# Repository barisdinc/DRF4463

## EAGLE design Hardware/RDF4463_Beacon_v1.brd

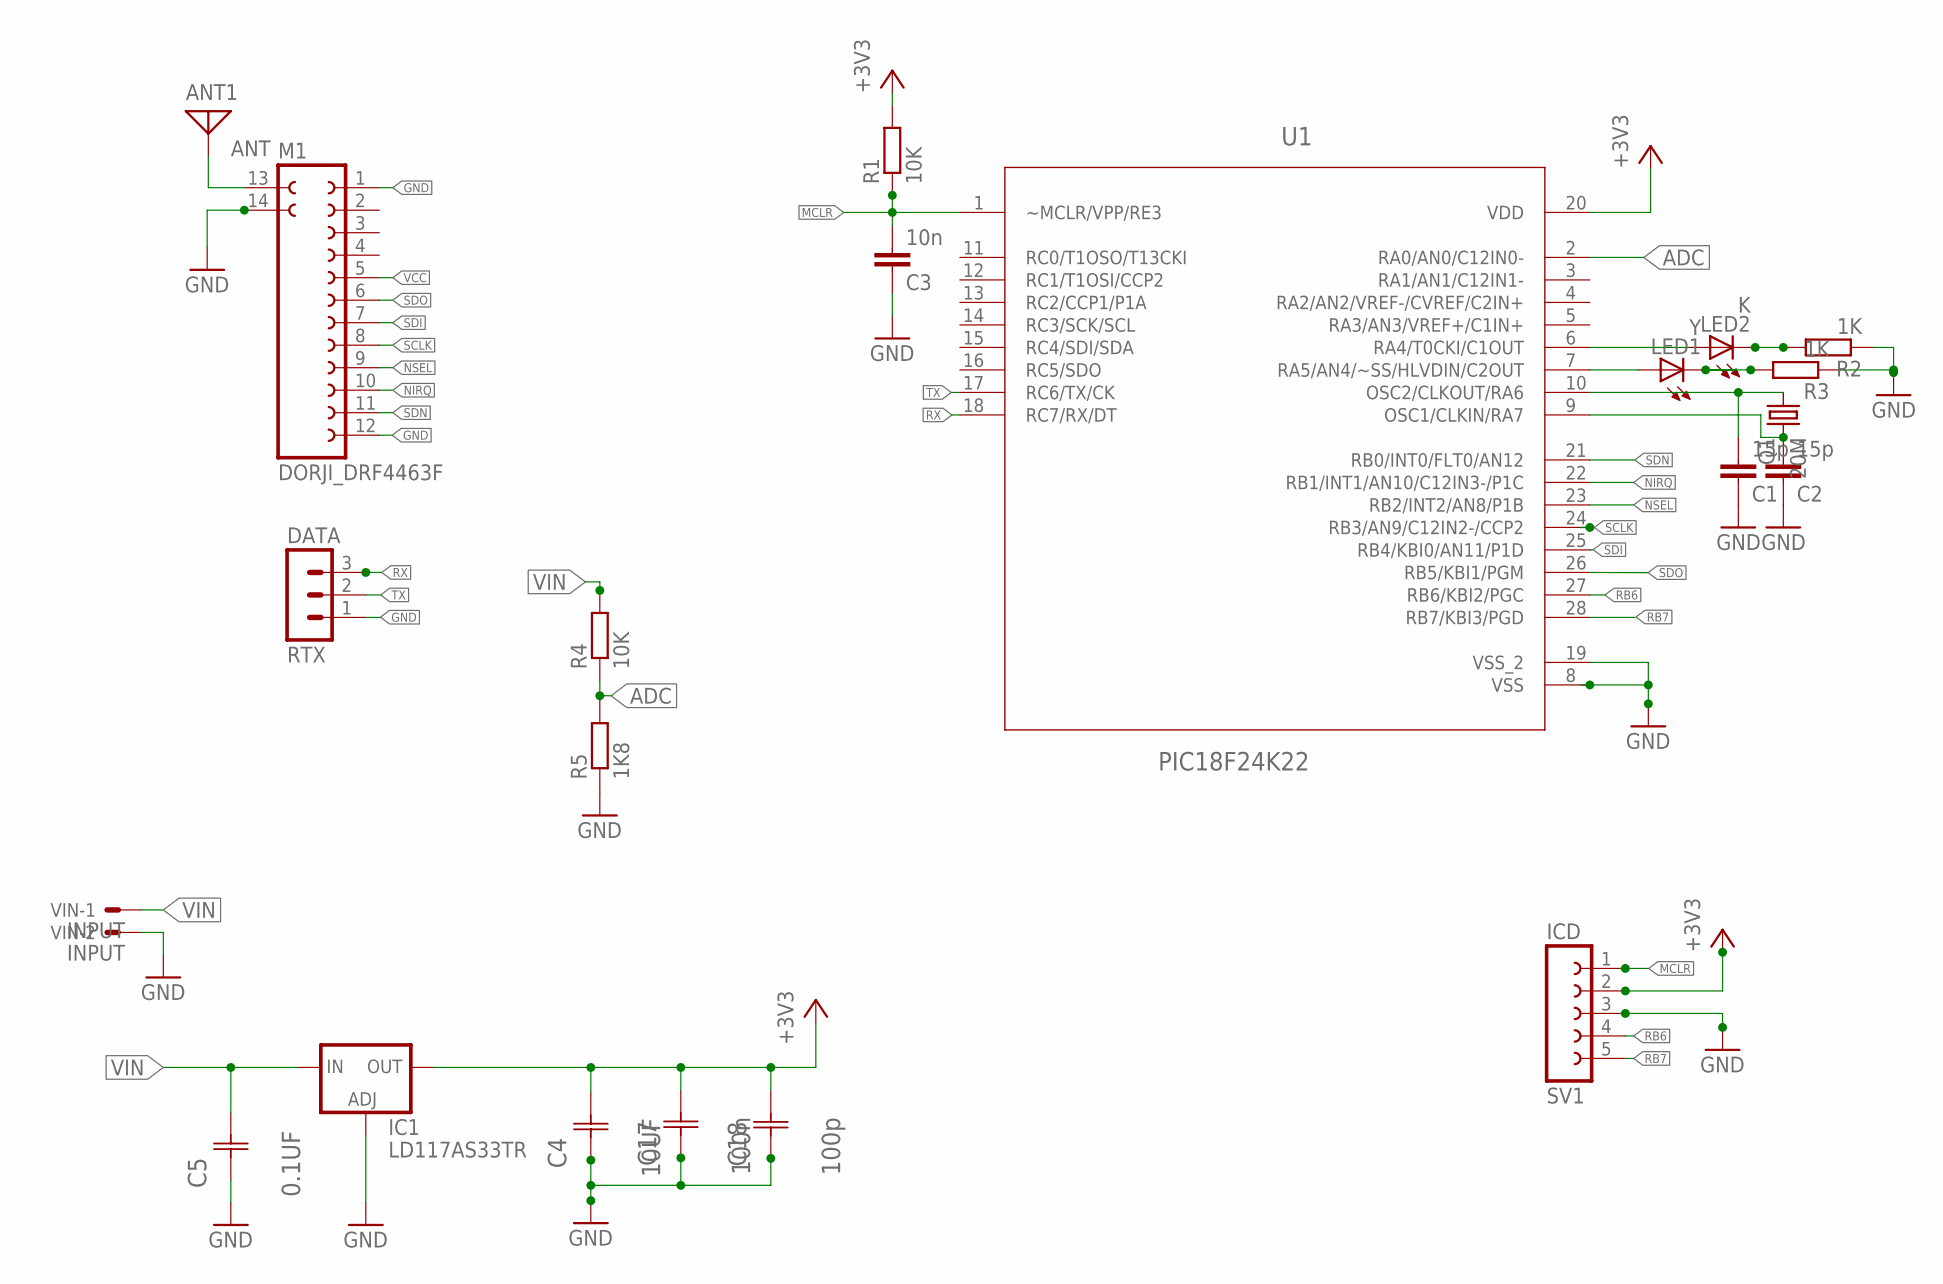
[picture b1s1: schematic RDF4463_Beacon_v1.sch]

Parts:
ANT1: ANT; PAD-01
C1, C2: 15p; C0805
C3: 10n; C0805
C4: 10UF; CAPC2013X140N
C5: 0.1UF; CAPC2012X94N
C17: 100n; CAPC2013X140N
C18: 100p; CAPC2013X140N
DATA: RTX; MA03-1
IC1: LD117AS33TR; SOT223
LED1: Y; SML0805
LED2: K; SML0805
M1: DORJI_DRF4463F
Q1: 20M; SM49
R1, R4: 10K; R0805
R2, R3: 1K; R0805
R5: 1K8; R0805
SV1: ICD; FE05-1
U1: PIC18F24K22; SSPO28
VIN: INPUT; KK-156-2

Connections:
ADC: R4.1, R5.2, U1.2 (RA0/AN0/C12IN0-)
GND: C1.1, C2.1, C3.1, C4.1 (C1), C5.1 (C1), C17.1 (C1), C18.1 (C1), DATA.1, IC1.1 (ADJ), M1.1, M1.12, M1.14, R2.1, R3.1, R5.1, SV1.3, U1.8 (VSS), U1.19 (VSS_2), VIN.2
MCLR: C3.2, R1.1, SV1.1, U1.1 (~MCLR/VPP/RE3)
unnamed: ANT1.1, M1.13
unnamed: C2.2, Q1.2, U1.9 (OSC1/CLKIN/RA7)
unnamed: C1.2, Q1.1, U1.10 (OSC2/CLKOUT/RA6)
unnamed: LED1.A, U1.7 (RA5/AN4/~SS/HLVDIN/C2OUT)
unnamed: LED2.A, U1.6 (RA4/T0CKI/C1OUT)
unnamed: LED2.C, R2.2
unnamed: LED1.C, R3.2
NIRQ: M1.10, U1.22 (RB1/INT1/AN10/C12IN3-/P1C)
NSEL: M1.9, U1.23 (RB2/INT2/AN8/P1B)
RB6: SV1.4, U1.27 (RB6/KBI2/PGC)
RB7: SV1.5, U1.28 (RB7/KBI3/PGD)
RX: DATA.3, U1.18 (RC7/RX/DT)
SCLK: M1.8, U1.24 (RB3/AN9/C12IN2-/CCP2)
SDI: M1.7, U1.25 (RB4/KBI0/AN11/P1D)
SDN: M1.11, U1.21 (RB0/INT0/FLT0/AN12)
SDO: M1.6, U1.26 (RB5/KBI1/PGM)
TX: DATA.2, U1.17 (RC6/TX/CK)
VCC: C4.2 (C2), C17.2 (C2), C18.2 (C2), IC1.4 (OUT), M1.5, R1.2, SV1.2, U1.20 (VDD)
VIN: C5.2 (C2), IC1.3 (IN), R4.2, VIN.1

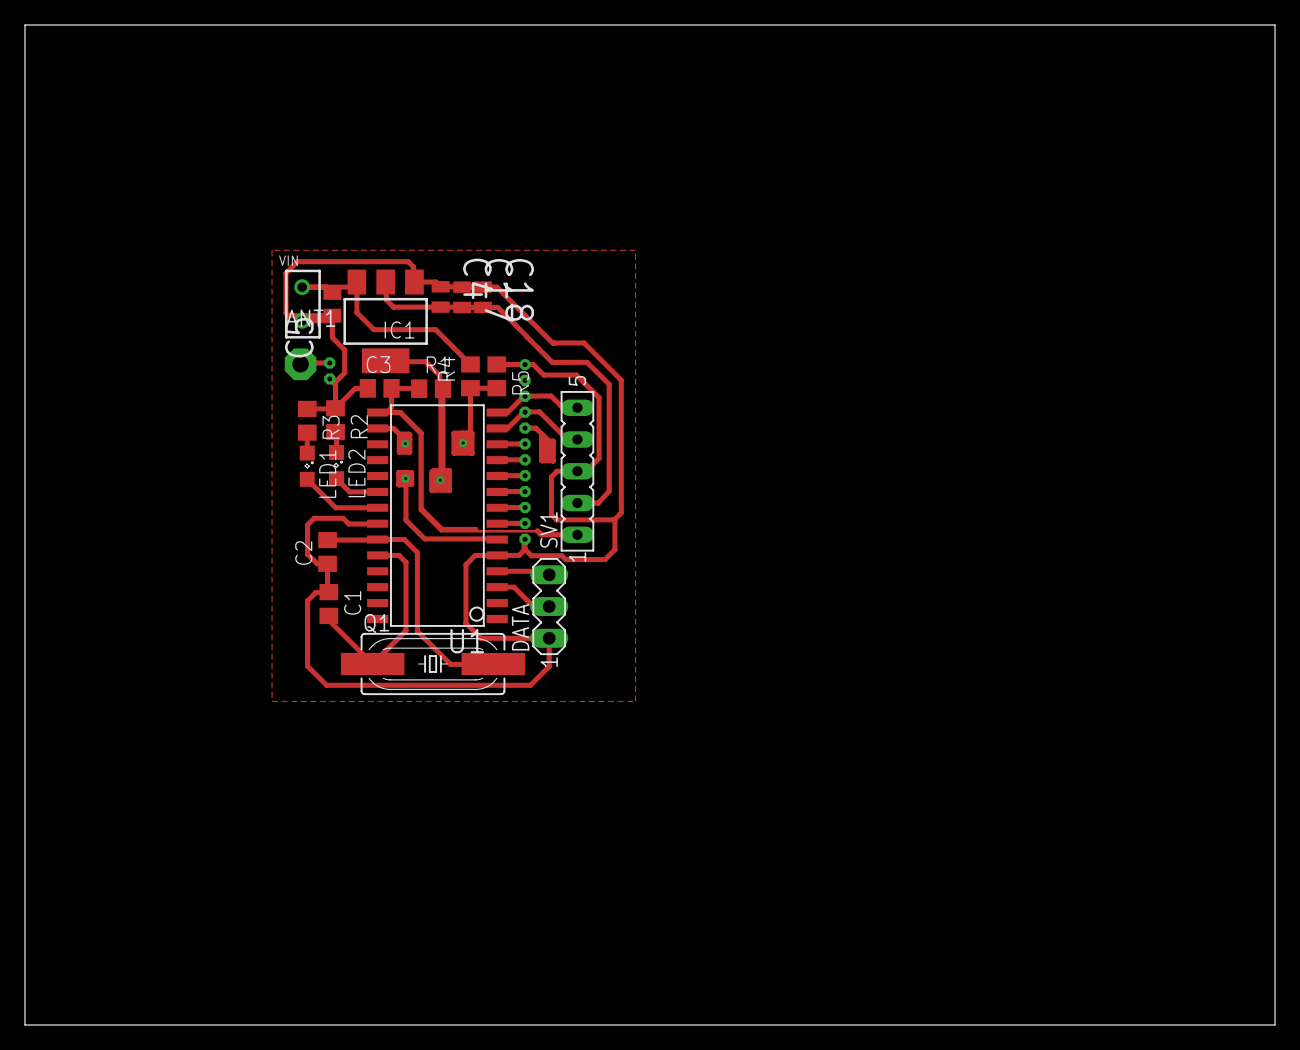
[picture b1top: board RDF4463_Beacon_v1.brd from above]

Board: 2 copper layers, 100.0 x 80.0 mm, 22 parts (1 on the bottom side), 22 nets.

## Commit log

2014-03-31 iilk commit
2014-04-01 Guncelleme
2014-04-02 PCB yi cizmeye basladim
2014-04-06 once -SS kilif a gore cizmistim
    Bu versiyonda degistiriyorum.. -SO klifli PIC e gorre yaptim
    bu kartin buyuk bir bolumunu ICD konnektoru ve DATA RXTX konnektoru tutuyor
    simdilik bunu bir EVALUATION karti gibi kullanacagim
    Daha sonra yapacaklarim sunlardir :
    ------------------------------------
    1) PIC'i APRS kullanimi icin 16F628 gibi kucuk bir PIC ile degistirmek
2014-04-09 Software dizinini ekledim
2014-04-09 ilk calisan kod.. sadece belli araliklarla sabit data/carrier basiyor
2014-04-12 icalisiyor
2014-04-12 Mors olarak calisiyor.. hersey WDS CONFIG den geliyor
2014-04-12 RAM kisminda duzenleme yaptim (Mors olarak calisiyor)
